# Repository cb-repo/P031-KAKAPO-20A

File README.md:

# KAKAPO - 20A v1.1

The KAKAPO *(ka-kuh-pow)* is a compact, all-in-one control and power platform that's designed to be the heart of your robot, removing setup headaches so you can focus on building and battling. It builds on the proven WEKA dual DC motor architecture, now adding integrated power switching, distribution, and dedicated outputs for light-weight servos or ESCs; streamlining your electronics without compromise.

The product is named after the [Kākāpō](https://en.wikipedia.org/wiki/K%C4%81k%C4%81p%C5%8D), a nocturnal flightless parrot endemic to New Zealand.

Developed, assembled, and tested in [Christchurch, New Zealand](https://www.google.co.nz/maps/place/Christchurch+New+Zealand), by Connor Benton.

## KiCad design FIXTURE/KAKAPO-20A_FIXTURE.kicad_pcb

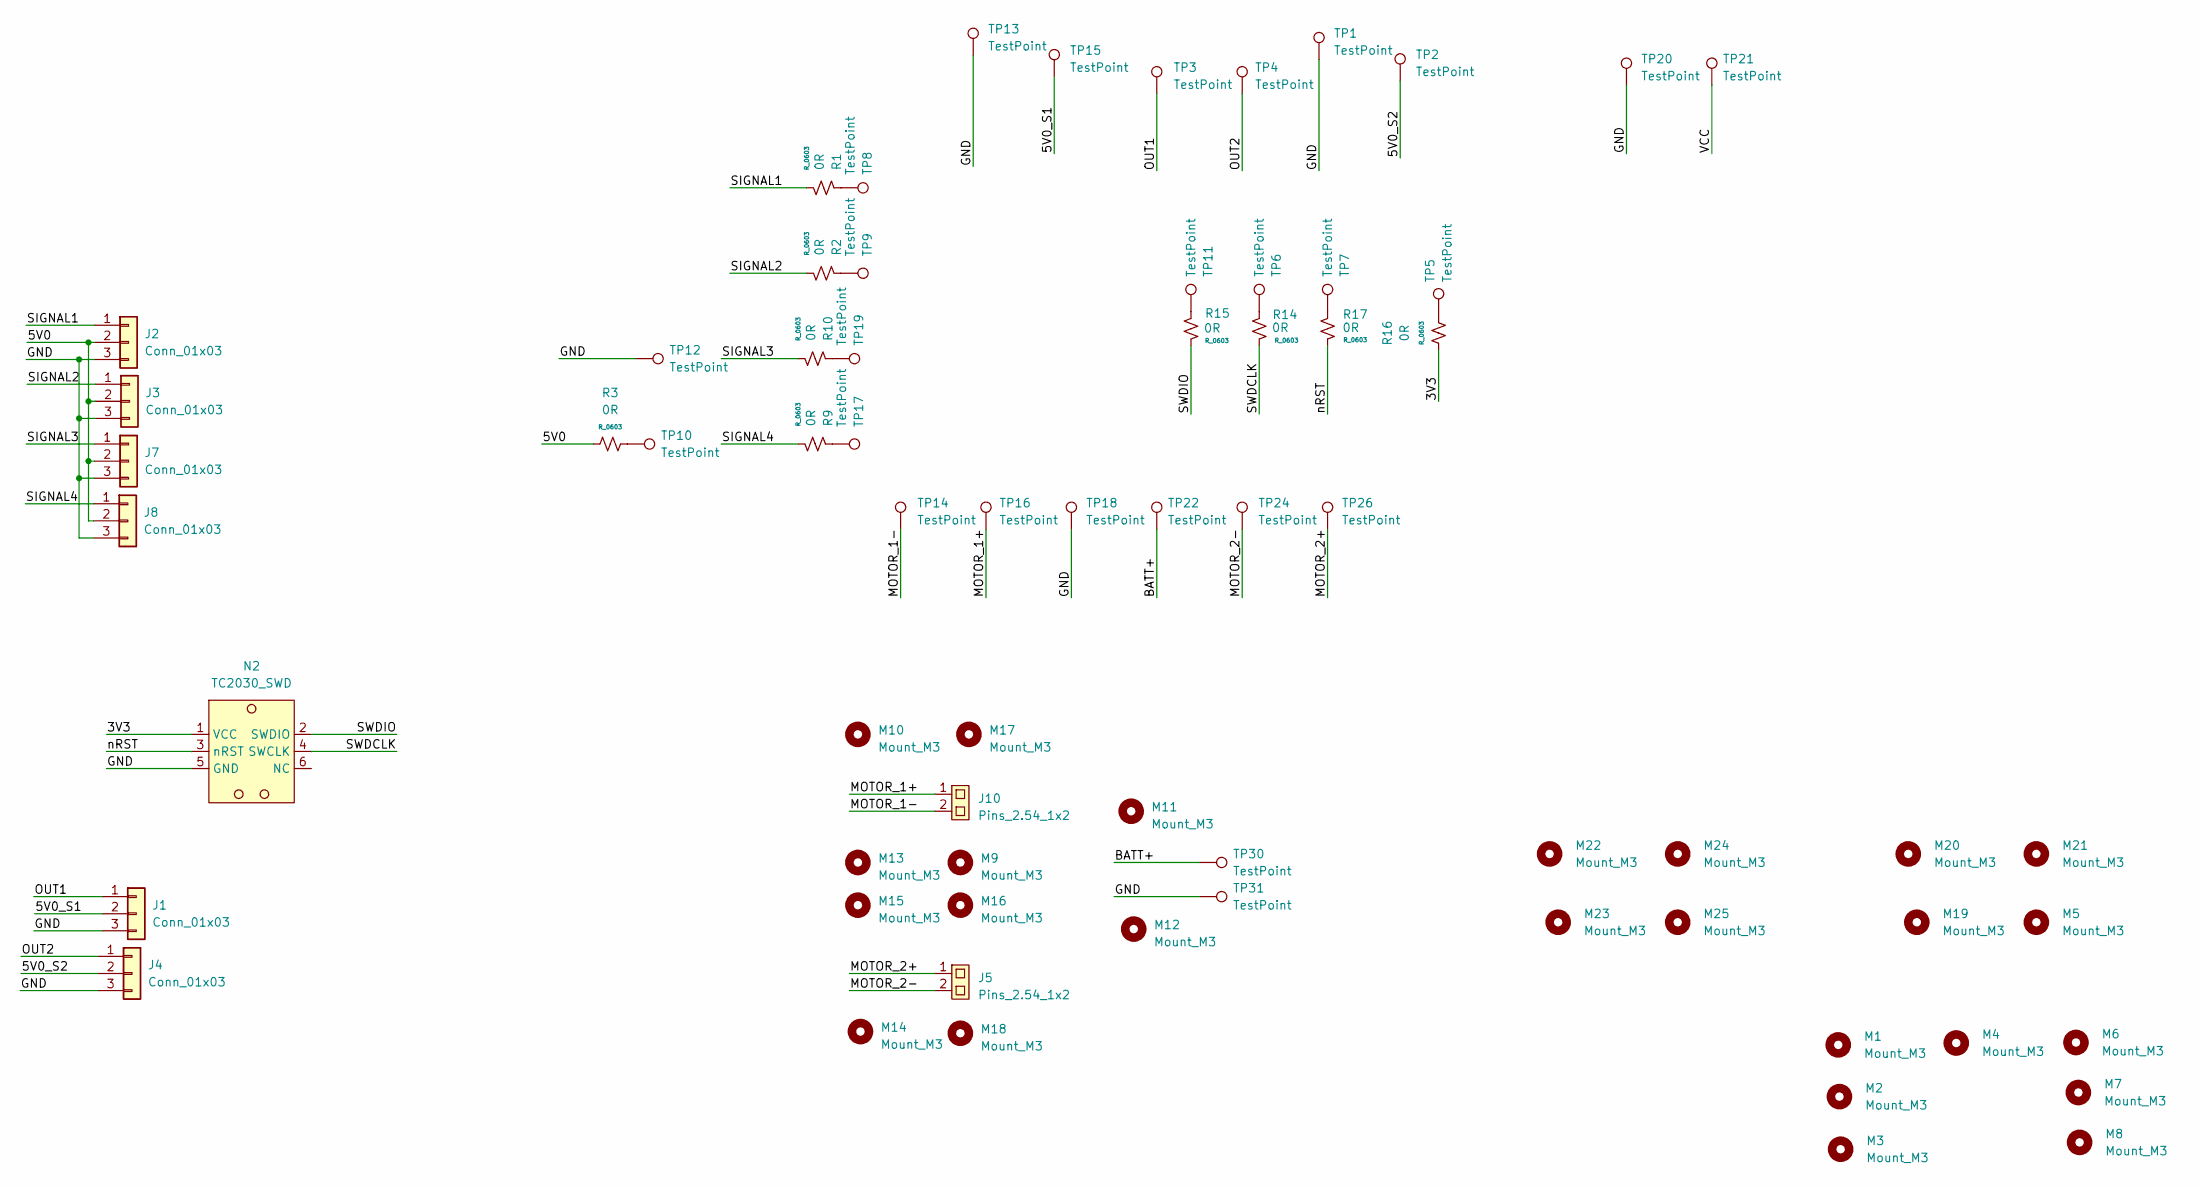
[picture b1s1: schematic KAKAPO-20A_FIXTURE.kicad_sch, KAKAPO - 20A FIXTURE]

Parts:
J1, J2, J3, J4, J7, J8: Conn_01x03; PinHeader_1x03_P2.54mm_Vertical
J5, J10: Pins_2.54_1x2; Pins-2.54-1x2
M1, M2, M3, M4, M5, M6, M7, M8, M9, M10, M11, M12, M13, M14, M15, M16, M17, M18, M19, M20, M21, M22, M23, M24, M25: Mount_M3
N2: TC2030_SWD; TagConnect_TC2030
R1, R2, R3, R9, R10, R14, R15, R16, R17: 0R; R_0603
TP1, TP2, TP3, TP4, TP5, TP6, TP7, TP8, TP9, TP10, TP11, TP12, TP13, TP14, TP15, TP16, TP17, TP18, TP19, TP20, TP21, TP22, TP24, TP26, TP30, TP31: TestPoint; TestPoint_THTPad_D3.0mm_Drill1.5mm

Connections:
/3V3: N2.1 (VCC), R16.1
/5V0: J2.2, J3.2, J7.2, J8.2, R3.1
/5V0_S1: J1.2, TP15.1
/5V0_S2: J4.2, TP2.1
/BATT+: TP22.1, TP30.1
/GND: J1.3, J2.3, J3.3, J4.3, J7.3, J8.3, N2.5 (GND), TP1.1, TP12.1, TP13.1, TP18.1, TP20.1, TP31.1
/MOTOR_1+: J10.1, TP16.1
/MOTOR_1-: J10.2, TP14.1
/MOTOR_2+: J5.1, TP26.1
/MOTOR_2-: J5.2, TP24.1
/OUT1: J1.1, TP3.1
/OUT2: J4.1, TP4.1
/SIGNAL1: J2.1, R1.2
/SIGNAL2: J3.1, R2.2
/SIGNAL3: J7.1, R10.2
/SIGNAL4: J8.1, R9.2
/SWDCLK: N2.4 (SWCLK), R14.2
/SWDIO: N2.2 (SWDIO), R15.2
/VCC: TP21.1
/nRST: N2.3 (nRST), R17.2
unnamed: R1.1, TP8.1
unnamed: R2.1, TP9.1
unnamed: R3.2, TP10.1
unnamed: R9.1, TP17.1
unnamed: R10.1, TP19.1
unnamed: R14.1, TP6.1
unnamed: R15.1, TP11.1
unnamed: R16.2, TP5.1
unnamed: R17.1, TP7.1

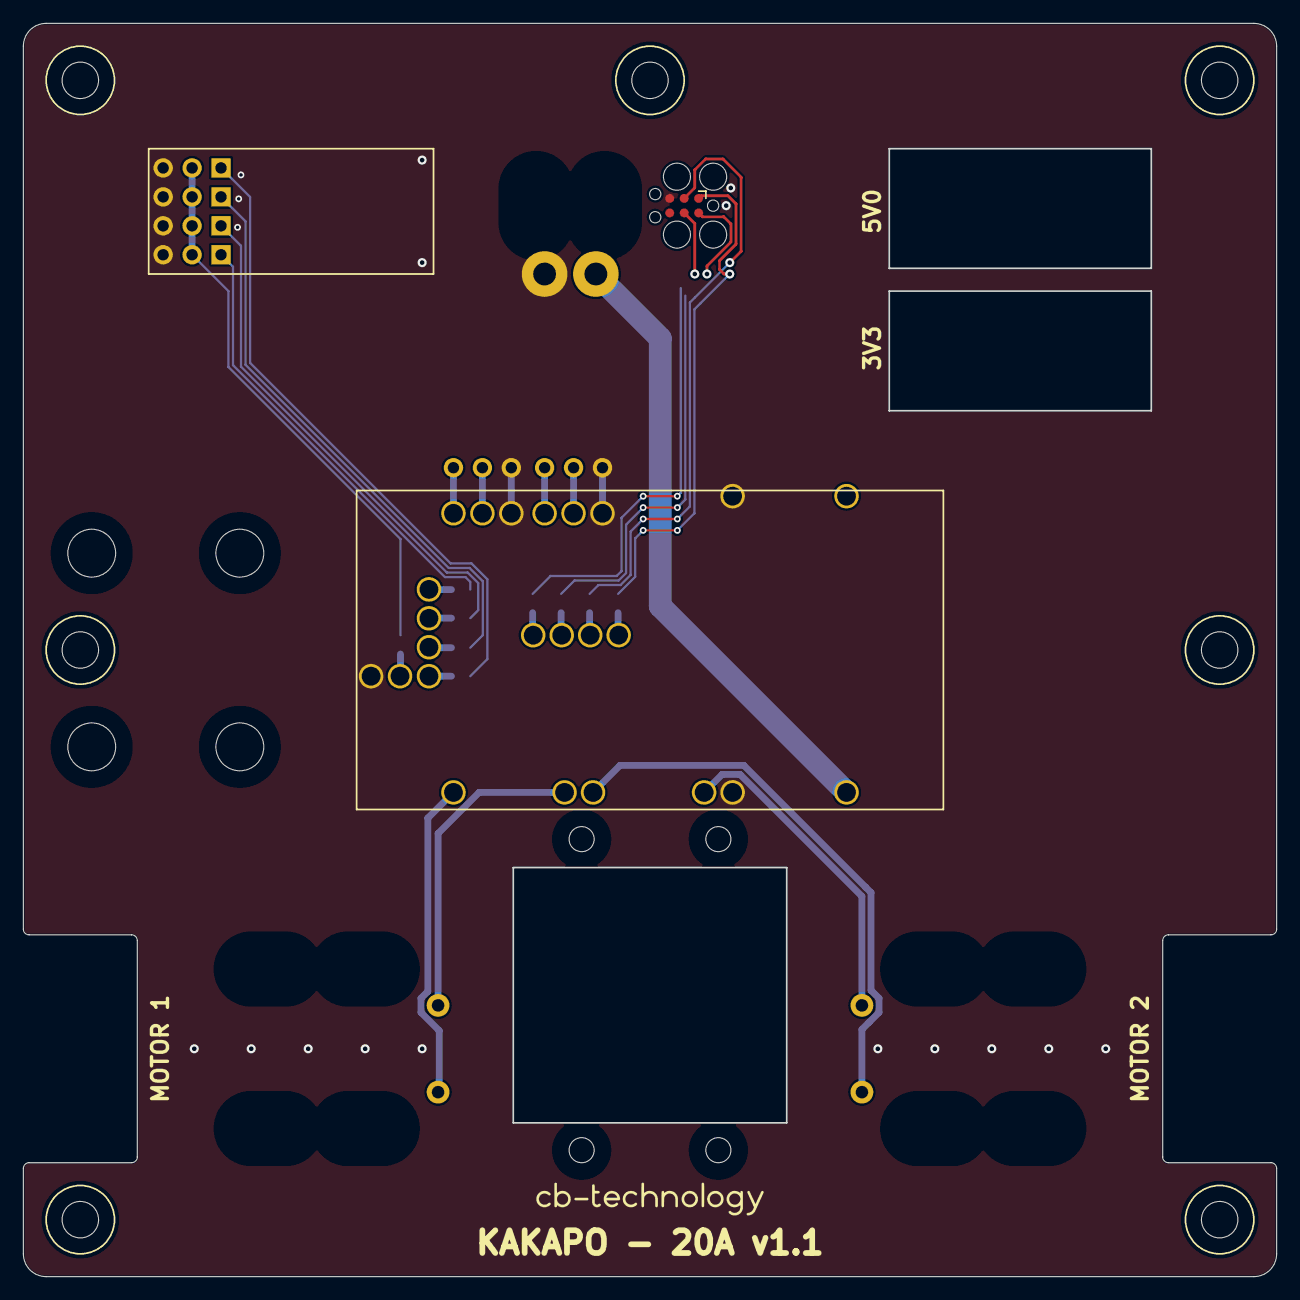
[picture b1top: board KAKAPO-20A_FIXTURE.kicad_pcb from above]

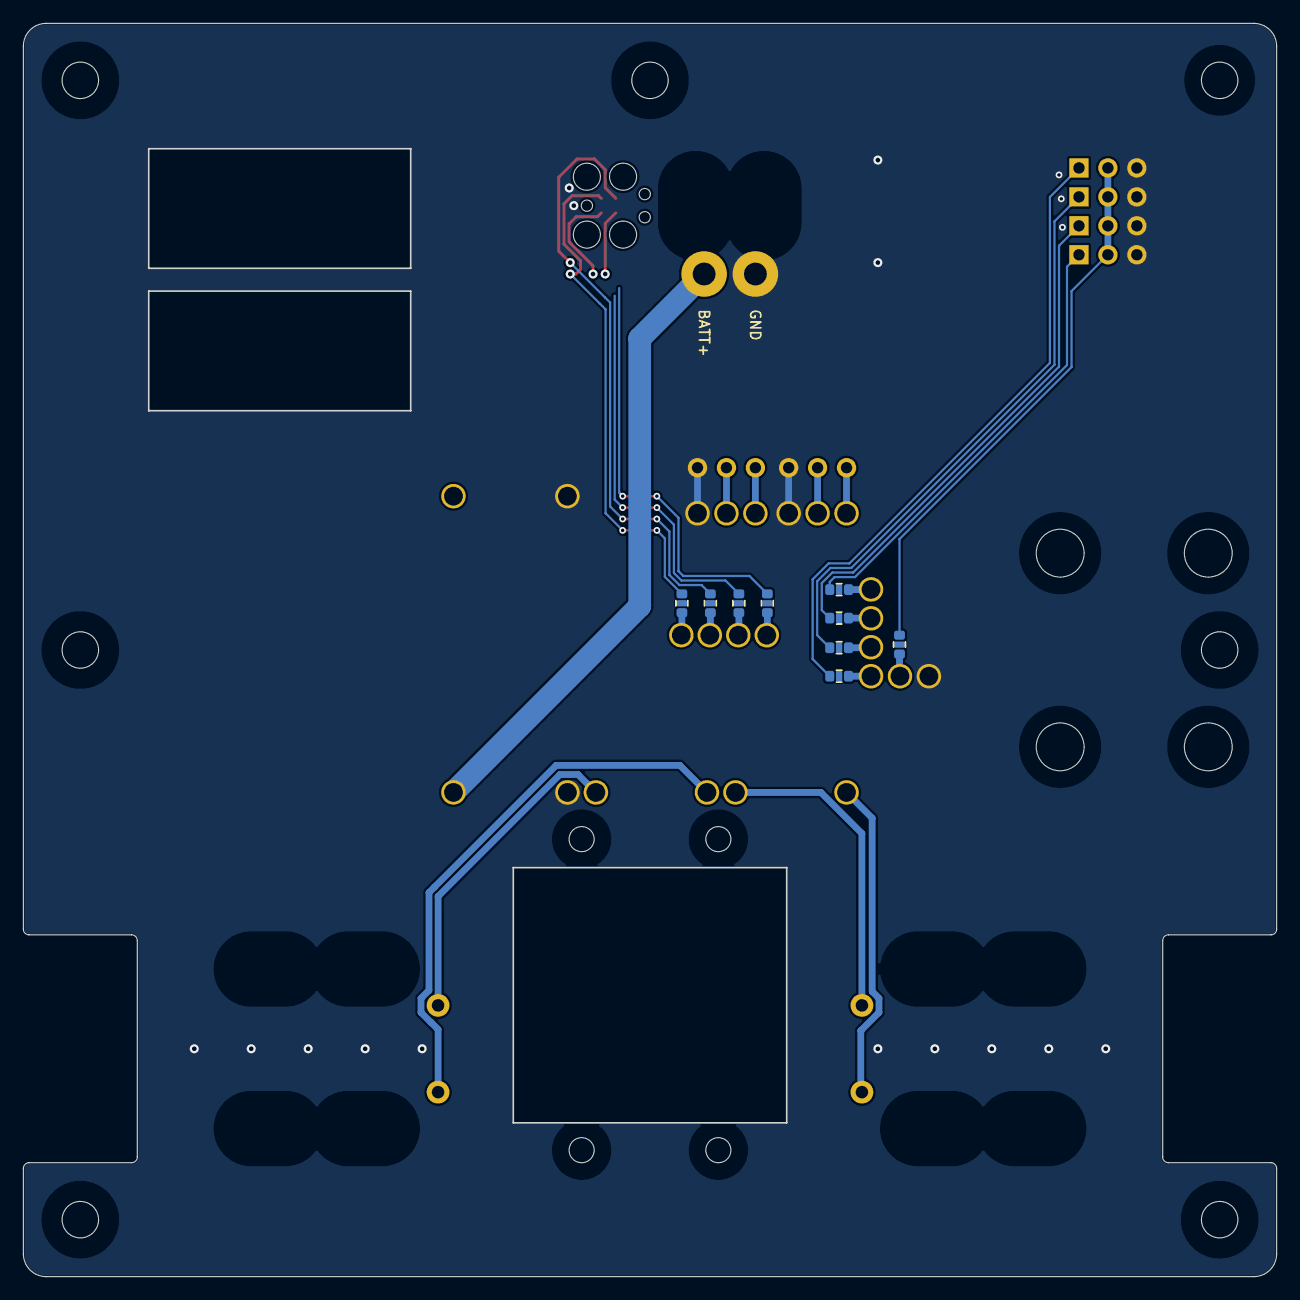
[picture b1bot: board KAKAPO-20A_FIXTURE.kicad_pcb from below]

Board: 2 copper layers, 110.0 x 110.0 mm, 69 parts (13 on the bottom side), 28 nets.

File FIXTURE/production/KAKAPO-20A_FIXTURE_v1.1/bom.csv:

Designator,Footprint,Quantity,Value,LCSC Part #
"J1, J2, J3, J4, J7, J8",PinHeader_1x03_P2.54mm_Vertical,6,Conn_01x03,
"J10, J5",Pins-2.54-1x2,2,Pins_2.54_1x2,
"R1, R10, R14, R15, R16, R17, R2, R3, R9",R_0603,9,0R,
"TP1, TP10, TP11, TP12, TP13, TP14, TP15, TP16, TP17, TP18, TP19, TP2, TP20, TP21, TP22, TP24, TP26, TP3, TP30, TP31, TP4, TP5, TP6, TP7, TP8, TP9",TestPoint_THTPad_D3.0mm_Drill1.5mm,26,TestPoint,

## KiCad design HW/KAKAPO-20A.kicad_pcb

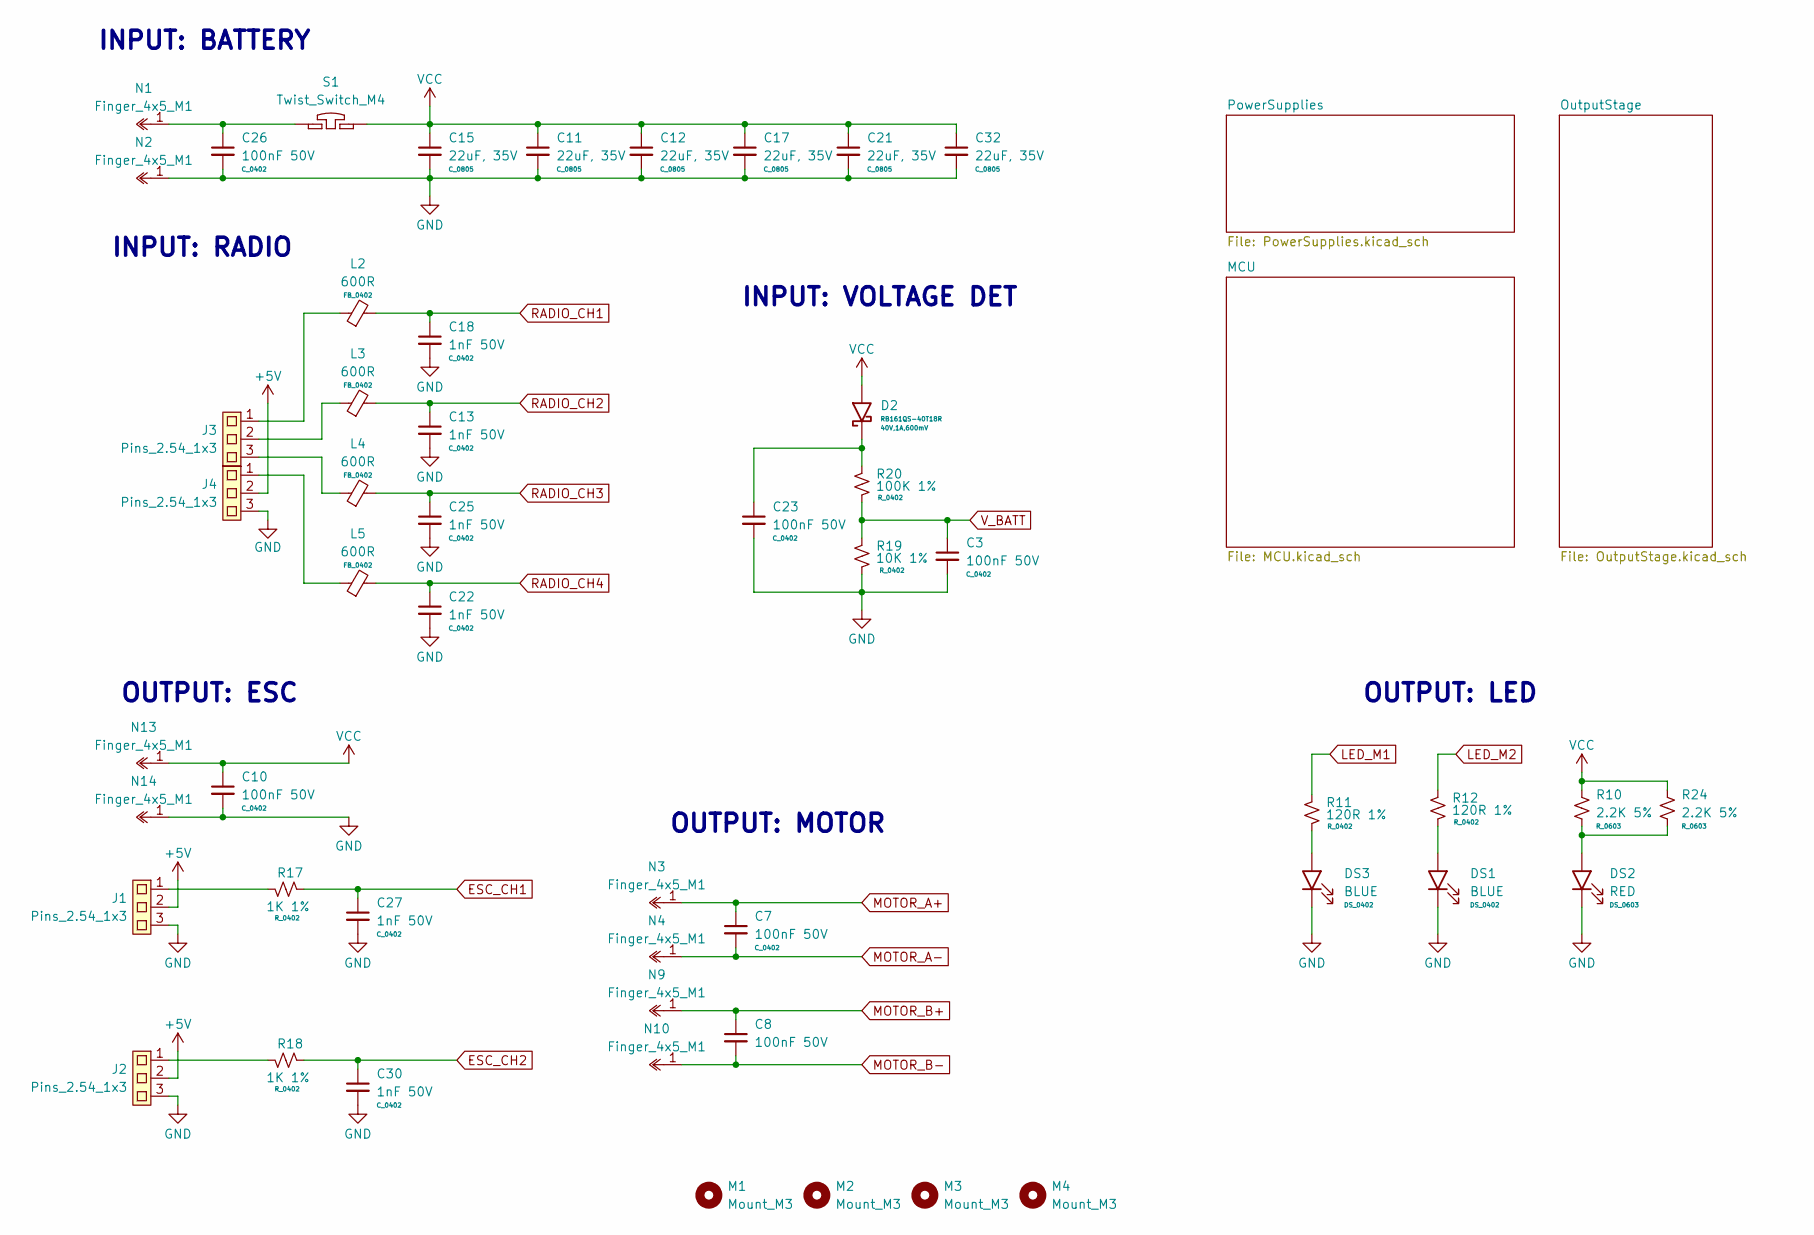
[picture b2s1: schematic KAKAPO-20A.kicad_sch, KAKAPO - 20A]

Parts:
C3, C7, C8, C10, C23, C26: 100nF 50V; C_0402; LCSC Part C105882
C11, C12, C15, C17, C21, C32: 22uF, 35V; C_0805; MFG Part HGC0805R5226M350NSLJ; LCSC Part C22367832
C13, C18, C22, C25, C27, C30: 1nF 50V; C_0402; LCSC Part C106205
D2: RB161QS-40T18R; R_0402; LCSC Part C2837790
DS1, DS3: BLUE; DS_0402; LCSC Part C965795
DS2: RED; DS_Everlight_IR21-21CL110TR8; MFG Part LTST-C230KRKT; LCSC Part C125107
J1, J2, J3, J4: Pins_2.54_1x3; Pins-2.54-1x3; LCSC Part C429954
L2, L3, L4, L5: 600R; FB_0402; MFG Part CBG100505U601T; LCSC Part C92618
M1, M2, M3, M4: Mount_M3
N1, N2, N3, N4, N9, N10, N13, N14: Finger_4x5_M1
R10, R24: 2.2K 5%; R_0603; MFG Part CRCW06032K20JNEAHP; LCSC Part C2077696
R11, R12: 120R 1%; R_0402; LCSC Part C114758
R17, R18: 1K 1%; R_0402; LCSC Part C2935237
R19: 10K 1%; R_0402; LCSC Part C60490
R20: 100K 1%; R_0402; LCSC Part C60491
S1: Twist_Switch_M4; MFG Part SMTSO4020MTJ; LCSC Part C2916373

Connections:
+5V: J1.2, J2.2, J4.2; also elsewhere on the board
ESC_CH1: C27.1, R17.2; also elsewhere on the board
ESC_CH2: C30.1, R18.2; also elsewhere on the board
GND: C3.2, C10.2, C11.2, C12.2, C13.2, C15.2, C17.2, C18.2, C21.2, C22.2, C23.2, C25.2, C26.2, C27.2, C30.2, C32.2, DS1.1 (K), DS2.1 (K), DS3.1 (K), J1.3, J2.3, J4.3, N2.1, N14.1, R19.2; also elsewhere on the board
LED_M1: R11.1; also elsewhere on the board
LED_M2: R12.1; also elsewhere on the board
MOTOR_A+: C7.1, N3.1; also elsewhere on the board
MOTOR_A-: C7.2, N4.1; also elsewhere on the board
MOTOR_B+: C8.1, N9.1; also elsewhere on the board
MOTOR_B-: C8.2, N10.1; also elsewhere on the board
unnamed: C23.1, D2.1, R20.1
unnamed: C26.1, N1.1, S1.2
unnamed: DS1.2 (A), R12.2
unnamed: DS2.2 (A), R10.2, R24.2
unnamed: DS3.2 (A), R11.2
unnamed: J1.1, R17.1
unnamed: J2.1, R18.1
unnamed: J3.1, L2.1
unnamed: J3.2, L3.1
unnamed: J3.3, L4.1
unnamed: J4.1, L5.1
RADIO_CH1: C18.1, L2.2; also elsewhere on the board
RADIO_CH2: C13.1, L3.2; also elsewhere on the board
RADIO_CH3: C25.1, L4.2; also elsewhere on the board
RADIO_CH4: C22.1, L5.2; also elsewhere on the board
VCC: C10.1, C11.1, C12.1, C15.1, C17.1, C21.1, C32.1, D2.2, N13.1, R10.1, R24.1, S1.1; also elsewhere on the board
V_BATT: C3.1, R19.1, R20.2; also elsewhere on the board

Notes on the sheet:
OUTPUT: MOTOR
OUTPUT: ESC
INPUT: RADIO
INPUT: VOLTAGE DET
OUTPUT: LED
INPUT: BATTERY

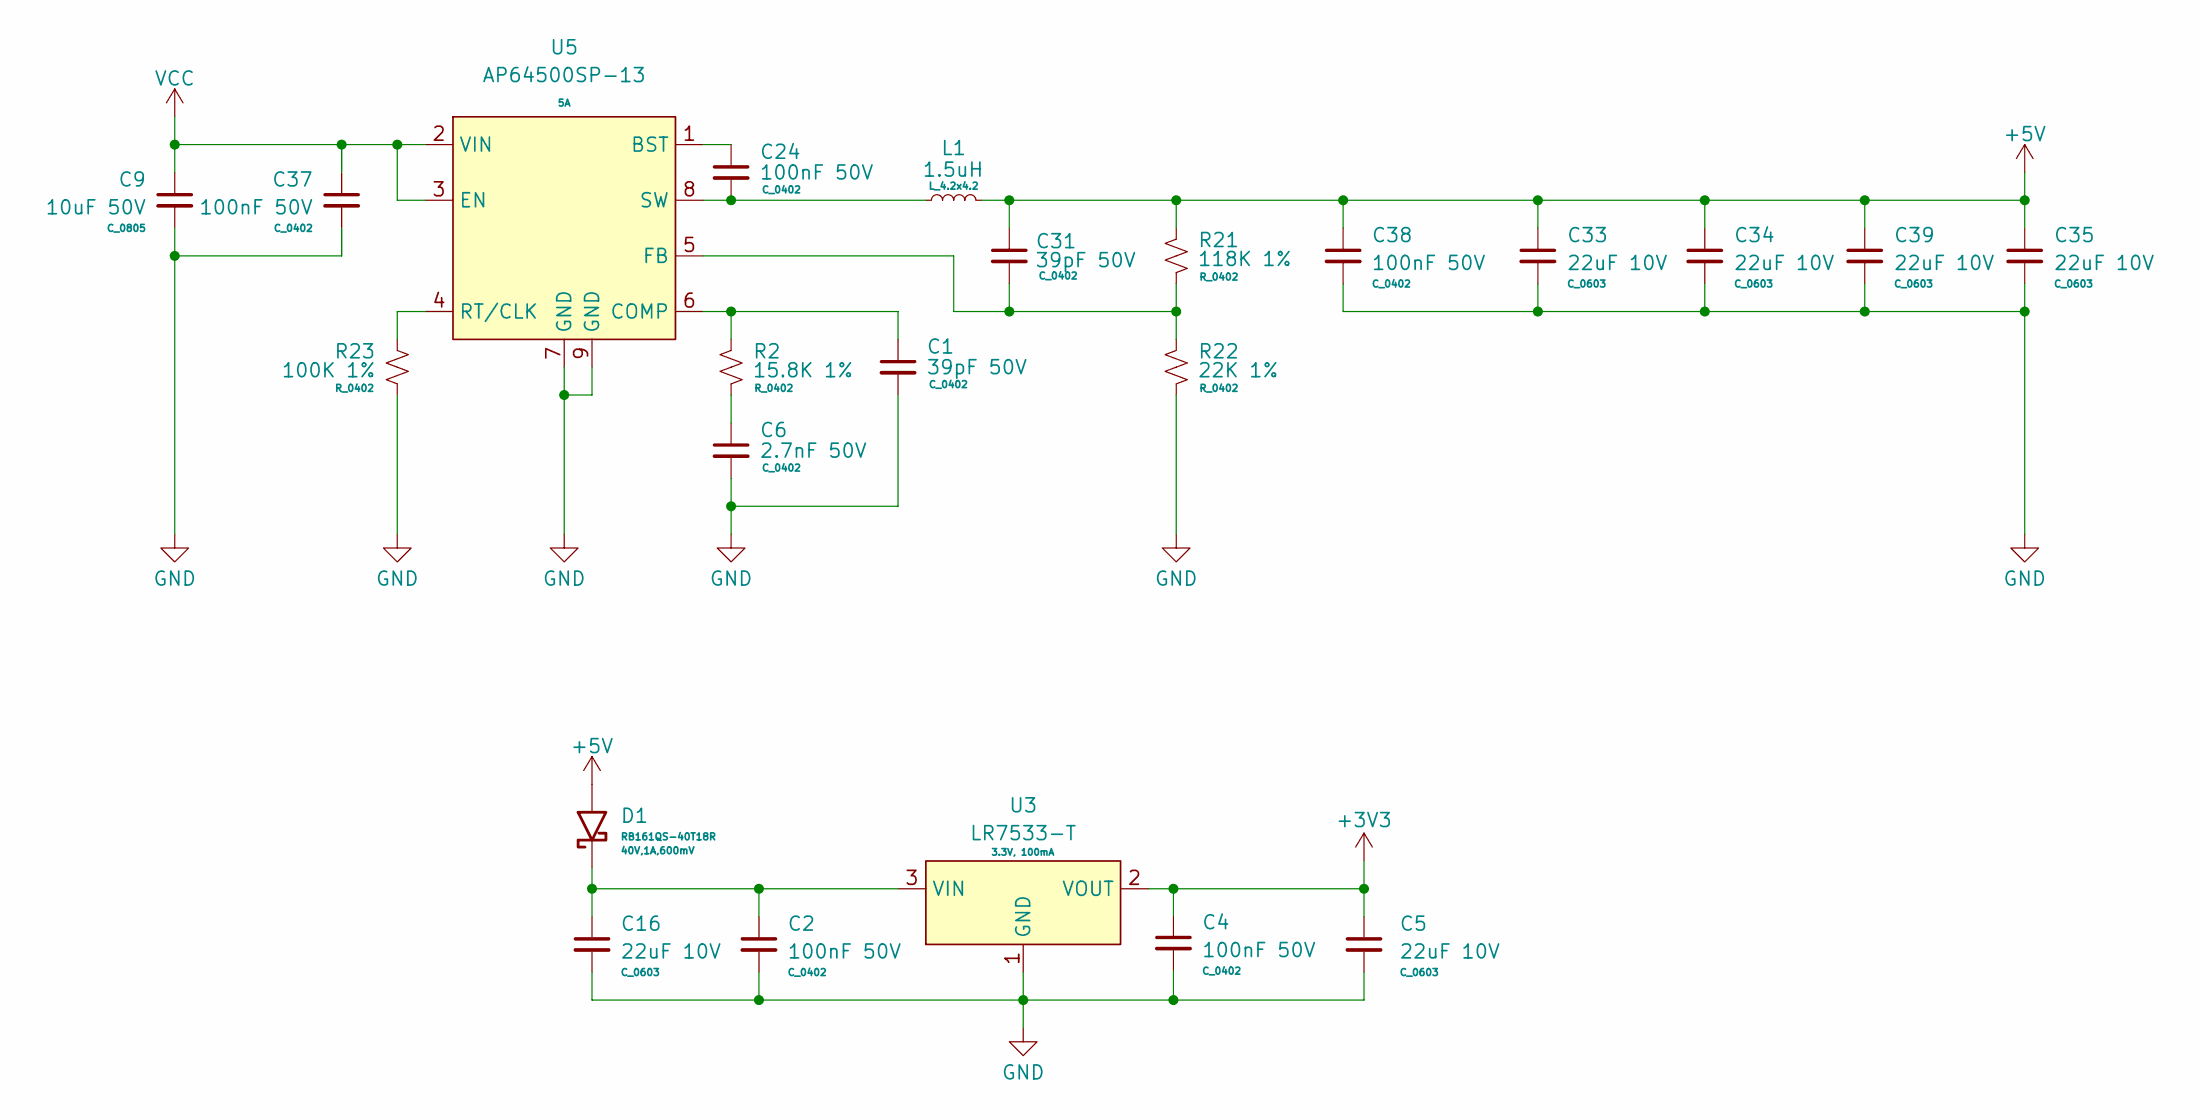
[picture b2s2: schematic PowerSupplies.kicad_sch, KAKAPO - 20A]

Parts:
C1, C31: 39pF 50V; C_0402; LCSC Part C106223
C2, C4, C24, C37, C38: 100nF 50V; C_0402; LCSC Part C105882
C5, C16, C33, C34, C35, C39: 22uF 10V; C_0603; LCSC Part C86295
C6: 2.7nF 50V; C_0402; LCSC Part C106251
C9: 10uF 50V; C_0805; MFG Part CL21A106KBYQNNE; LCSC Part C2932476
D1: RB161QS-40T18R; R_0402; LCSC Part C2837790
L1: 1.5uH; L_4.2x4.2; MFG Part BCIHP0420SC-1R5M; LCSC Part C2921165
R2: 15.8K 1%; R_0402; LCSC Part C26956
R21: 118K 1%; R_0402; LCSC Part C5126219
R22: 22K 1%; R_0402; LCSC Part C2909337
R23: 100K 1%; R_0402; LCSC Part C60491
U3: LR7533-T; SOT23_3; MFG Part LR7533-T; LCSC Part C486069
U5: AP64500SP-13; SOIC_8_EP; LCSC Part C2070920

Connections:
+3V3: C4.1, C5.1, U3.2 (VOUT); also elsewhere on the board
+5V: C31.1, C33.1, C34.1, C35.1, C38.1, C39.1, D1.2, L1.2, R21.1; also elsewhere on the board
GND: C1.2, C2.2, C4.2, C5.2, C6.2, C9.2, C16.2, C33.2, C34.2, C35.2, C37.2, C38.2, C39.2, R22.2, R23.2, U3.1 (GND), U5.7 (GND), U5.9 (GND); also elsewhere on the board
unnamed: C6.1, R2.2
unnamed: C2.1, C16.1, D1.1, U3.3 (VIN)
unnamed: C24.1, U5.1 (BST)
unnamed: C1.1, R2.1, U5.6 (COMP)
unnamed: C31.2, R21.2, R22.1, U5.5 (FB)
unnamed: R23.1, U5.4 (RT/CLK)
unnamed: C24.2, L1.1, U5.8 (SW)
VCC: C9.1, C37.1, U5.2 (VIN), U5.3 (EN); also elsewhere on the board

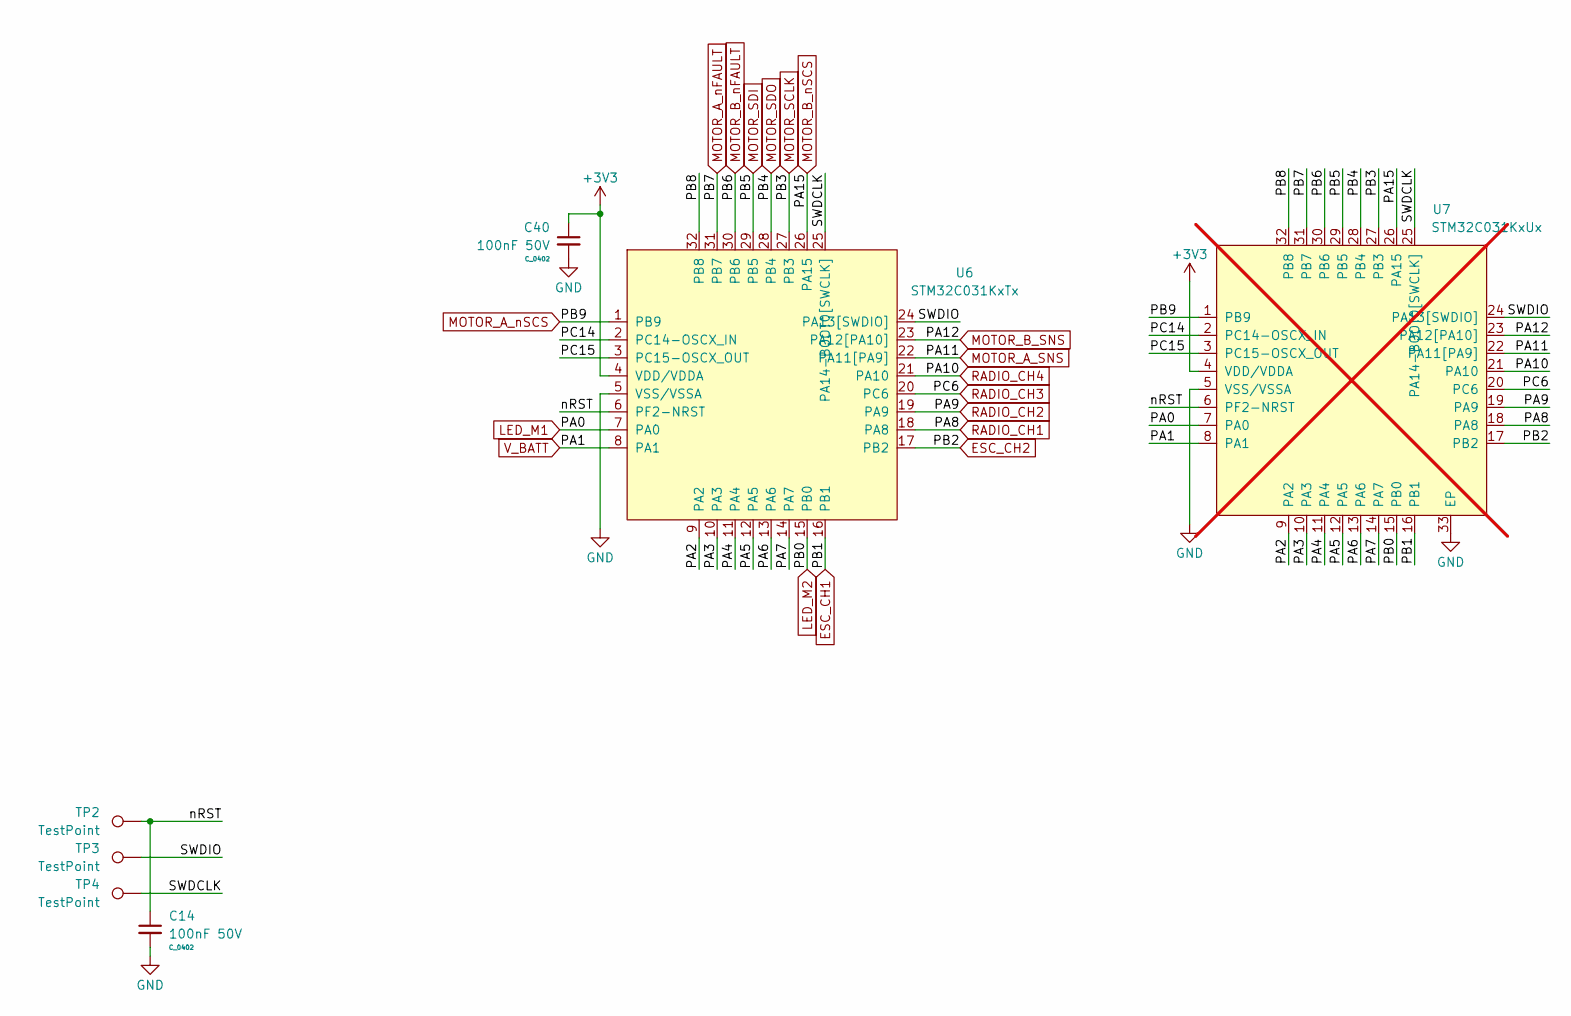
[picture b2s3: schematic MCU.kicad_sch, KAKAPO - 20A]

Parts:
C14, C40: 100nF 50V; C_0402; LCSC Part C105882
TP2, TP3, TP4: TestPoint; TestPoint_Pad_D1.5mm
U6: STM32C031KxTx; LQFP32_08_7x7
U7: STM32C031KxUx; QFN32_05_5x5_EP; not fitted

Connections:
+3V3: C40.1, U6.4 (VDD/VDDA), U7.4 (VDD/VDDA); also elsewhere on the board
/MCU/PA2: U6.9 (PA2), U7.9 (PA2)
/MCU/PA3: U6.10 (PA3), U7.10 (PA3)
/MCU/PA4: U6.11 (PA4), U7.11 (PA4)
/MCU/PA5: U6.12 (PA5), U7.12 (PA5)
/MCU/PA6: U6.13 (PA6), U7.13 (PA6)
/MCU/PA7: U6.14 (PA7), U7.14 (PA7)
/MCU/PB8: U6.32 (PB8), U7.32 (PB8)
/MCU/PC14: U6.2 (PC14-OSCX_IN), U7.2 (PC14-OSCX_IN)
/MCU/PC15: U6.3 (PC15-OSCX_OUT), U7.3 (PC15-OSCX_OUT)
/MCU/SWDCLK: TP4.1, U6.25 (PA14-BOOT0[SWCLK]), U7.25 (PA14-BOOT0[SWCLK])
/MCU/SWDIO: TP3.1, U6.24 (PA13[SWDIO]), U7.24 (PA13[SWDIO])
/MCU/nRST: C14.1, TP2.1, U6.6 (PF2-NRST), U7.6 (PF2-NRST)
ESC_CH1: U6.16 (PB1), U7.16 (PB1); also elsewhere on the board
ESC_CH2: U6.17 (PB2), U7.17 (PB2); also elsewhere on the board
GND: C14.2, C40.2, U6.5 (VSS/VSSA), U7.5 (VSS/VSSA), U7.33 (EP); also elsewhere on the board
LED_M1: U6.7 (PA0), U7.7 (PA0); also elsewhere on the board
LED_M2: U6.15 (PB0), U7.15 (PB0); also elsewhere on the board
MOTOR_A_SNS: U6.22 (PA11[PA9]), U7.22 (PA11[PA9]); also elsewhere on the board
MOTOR_A_nFAULT: U6.31 (PB7), U7.31 (PB7); also elsewhere on the board
MOTOR_A_nSCS: U6.1 (PB9), U7.1 (PB9); also elsewhere on the board
MOTOR_B_SNS: U6.23 (PA12[PA10]), U7.23 (PA12[PA10]); also elsewhere on the board
MOTOR_B_nFAULT: U6.30 (PB6), U7.30 (PB6); also elsewhere on the board
MOTOR_B_nSCS: U6.26 (PA15), U7.26 (PA15); also elsewhere on the board
MOTOR_SCLK: U6.27 (PB3), U7.27 (PB3); also elsewhere on the board
MOTOR_SDI: U6.29 (PB5), U7.29 (PB5); also elsewhere on the board
MOTOR_SDO: U6.28 (PB4), U7.28 (PB4); also elsewhere on the board
RADIO_CH1: U6.18 (PA8), U7.18 (PA8); also elsewhere on the board
RADIO_CH2: U6.19 (PA9), U7.19 (PA9); also elsewhere on the board
RADIO_CH3: U6.20 (PC6), U7.20 (PC6); also elsewhere on the board
RADIO_CH4: U6.21 (PA10), U7.21 (PA10); also elsewhere on the board
V_BATT: U6.8 (PA1), U7.8 (PA1); also elsewhere on the board

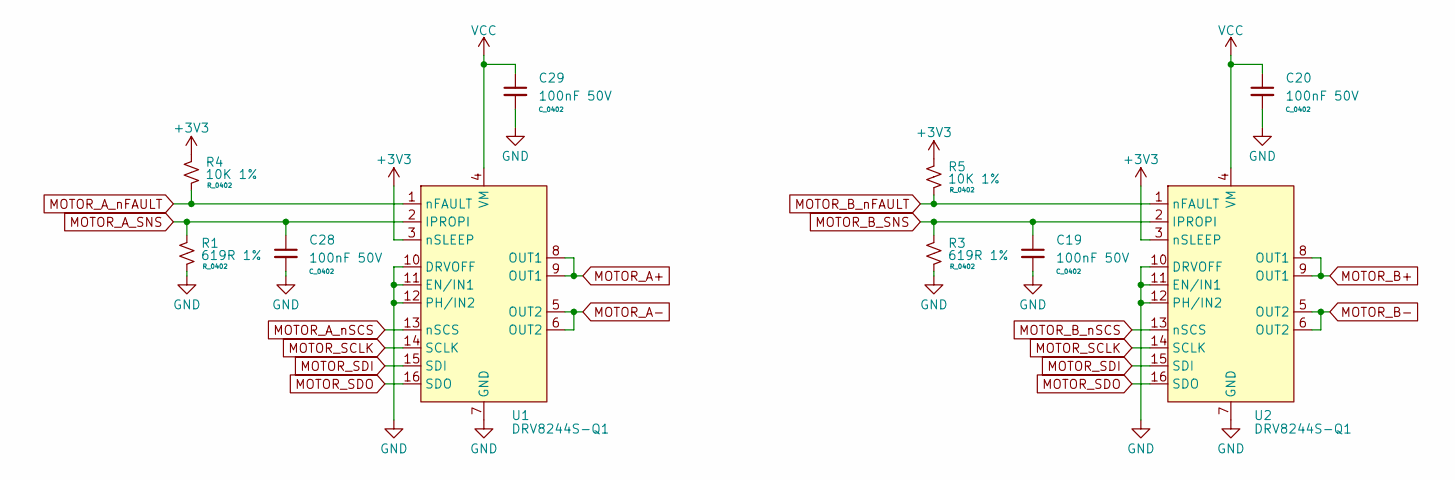
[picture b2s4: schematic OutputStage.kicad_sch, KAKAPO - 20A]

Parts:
C19, C20, C28, C29: 100nF 50V; C_0402; LCSC Part C105882
R1, R3: 619R 1%; R_0402; LCSC Part C5121525
R4, R5: 10K 1%; R_0402; LCSC Part C60490
U1, U2: DRV8244S-Q1; VQFN-HR-16; LCSC Part C3681071

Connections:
+3V3: R4.1, R5.1, U1.3 (nSLEEP), U2.3 (nSLEEP); also elsewhere on the board
GND: C19.2, C20.2, C28.2, C29.2, R1.2, R3.2, U1.7 (GND), U1.10 (DRVOFF), U1.11 (EN/IN1), U1.12 (PH/IN2), U2.7 (GND), U2.10 (DRVOFF), U2.11 (EN/IN1), U2.12 (PH/IN2); also elsewhere on the board
MOTOR_A+: U1.8 (OUT1), U1.9 (OUT1); also elsewhere on the board
MOTOR_A-: U1.5 (OUT2), U1.6 (OUT2); also elsewhere on the board
MOTOR_A_SNS: C28.1, R1.1, U1.2 (IPROPI); also elsewhere on the board
MOTOR_A_nFAULT: R4.2, U1.1 (nFAULT); also elsewhere on the board
MOTOR_A_nSCS: U1.13 (nSCS); also elsewhere on the board
MOTOR_B+: U2.8 (OUT1), U2.9 (OUT1); also elsewhere on the board
MOTOR_B-: U2.5 (OUT2), U2.6 (OUT2); also elsewhere on the board
MOTOR_B_SNS: C19.1, R3.1, U2.2 (IPROPI); also elsewhere on the board
MOTOR_B_nFAULT: R5.2, U2.1 (nFAULT); also elsewhere on the board
MOTOR_B_nSCS: U2.13 (nSCS); also elsewhere on the board
MOTOR_SCLK: U1.14 (SCLK), U2.14 (SCLK); also elsewhere on the board
MOTOR_SDI: U1.15 (SDI), U2.15 (SDI); also elsewhere on the board
MOTOR_SDO: U1.16 (SDO), U2.16 (SDO); also elsewhere on the board
VCC: C20.1, C29.1, U1.4 (VM), U2.4 (VM); also elsewhere on the board

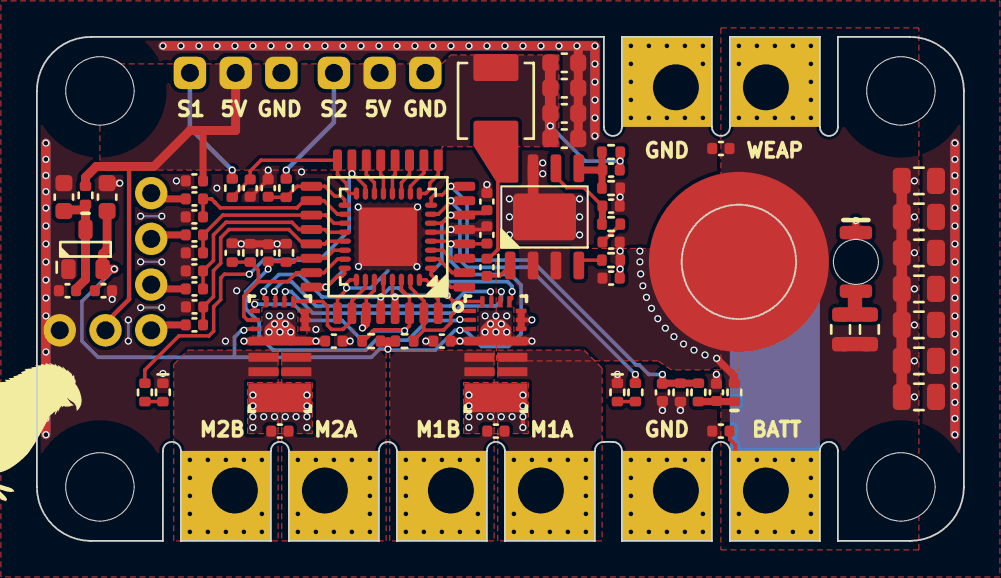
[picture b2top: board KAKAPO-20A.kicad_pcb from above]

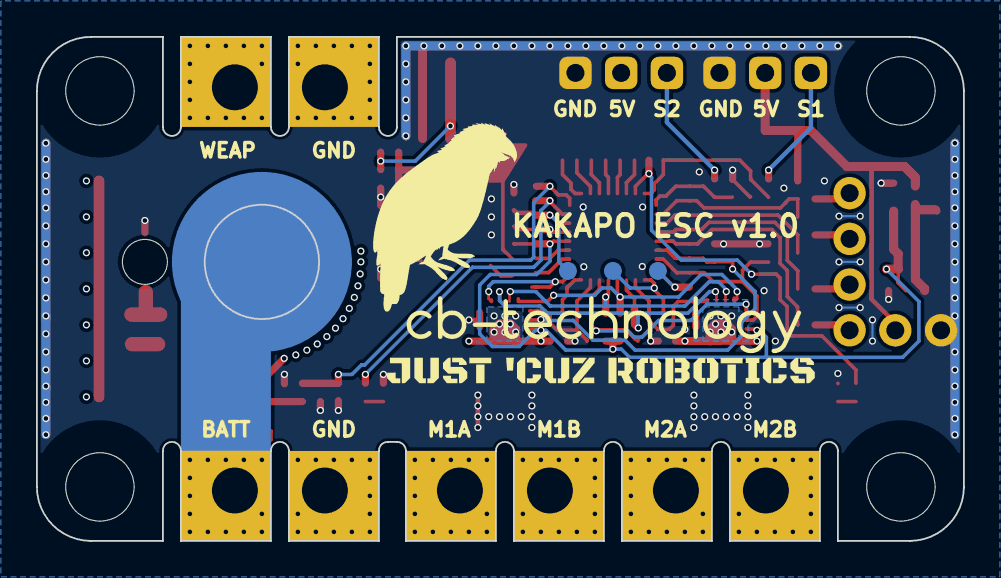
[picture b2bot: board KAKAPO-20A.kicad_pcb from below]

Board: 4 copper layers, 51.5 x 28.0 mm, 91 parts (7 on the bottom side), 56 nets.

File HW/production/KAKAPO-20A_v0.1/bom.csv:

Designator,Footprint,Quantity,Value,LCSC Part #
C1,C_0402,1,39pF 50V,C105882
"C10, C14, C19, C2, C20, C23, C24, C26, C28, C29, C3, C37, C38, C4, C40, C7, C8",C_0402,17,100nF 50V,C105882
"C11, C12, C15, C17, C21, C32",C_0805,6,"22uF, 35V",
"C13, C18, C22, C25, C27, C30",C_0402,6,1nF 50V,C106205
"C16, C33, C34, C35, C39, C5",C_0603,6,22uF 10V,C86295
C31,C_0402,1,39pF 50V,
C6,C_0402,1,2.7nF 50V,
C9,C_0805,1,10uF 50V,C2932476
"D1, D2",R_0402,2,RB161QS-40T18R,C2837790
"DS1, DS3",DS_0402,2,BLUE,C965795
DS2,DS_Everlight_IR21-21CL110TR8,1,RED,
"J1, J2, J3, J4",Pins-2.54-1x3,4,Pins_2.54_1x3,
L1,L_4.2x4.2,1,1.5uH,
"L2, L3, L4, L5",FB_0402,4,600R,
"R1, R3",R_0402,2,619R 1%,C309549
"R10, R24",R_0603,2,2.2K 5% ,
"R11, R12",R_0402,2,120R 1%,C114758
"R17, R18",R_0402,2,1K 1%,C2935237
R19,R_0402,1,10K 1%,C60490
R2,R_0402,1,15.8K 1%,
R20,R_0402,1,100K 1%,C60491
R21,R_0402,1,115.8K 1%,
R22,R_0402,1,22.1K 1%,C226367
R23,R_0402,1,100K 1%,
"R4, R5",R_0402,2,10K 1%,C309549
S1,Twist_Switch_M4,1,Twist_Switch_M4,
"TP2, TP3, TP4",TestPoint_Pad_D1.5mm,3,TestPoint,
"U1, U2",VQFN-HR-16,2,DRV8244S-Q1,C3681071
U3,SOT23_3,1,LR7533-T,C486069
U5,SOIC_8_EP,1,AP64500SP-13,
U6,LQFP32_08_7x7,1,STM32C031KxTx,
U7,QFN32_05_5x5_EP,1,STM32C031KxUx,DNP
